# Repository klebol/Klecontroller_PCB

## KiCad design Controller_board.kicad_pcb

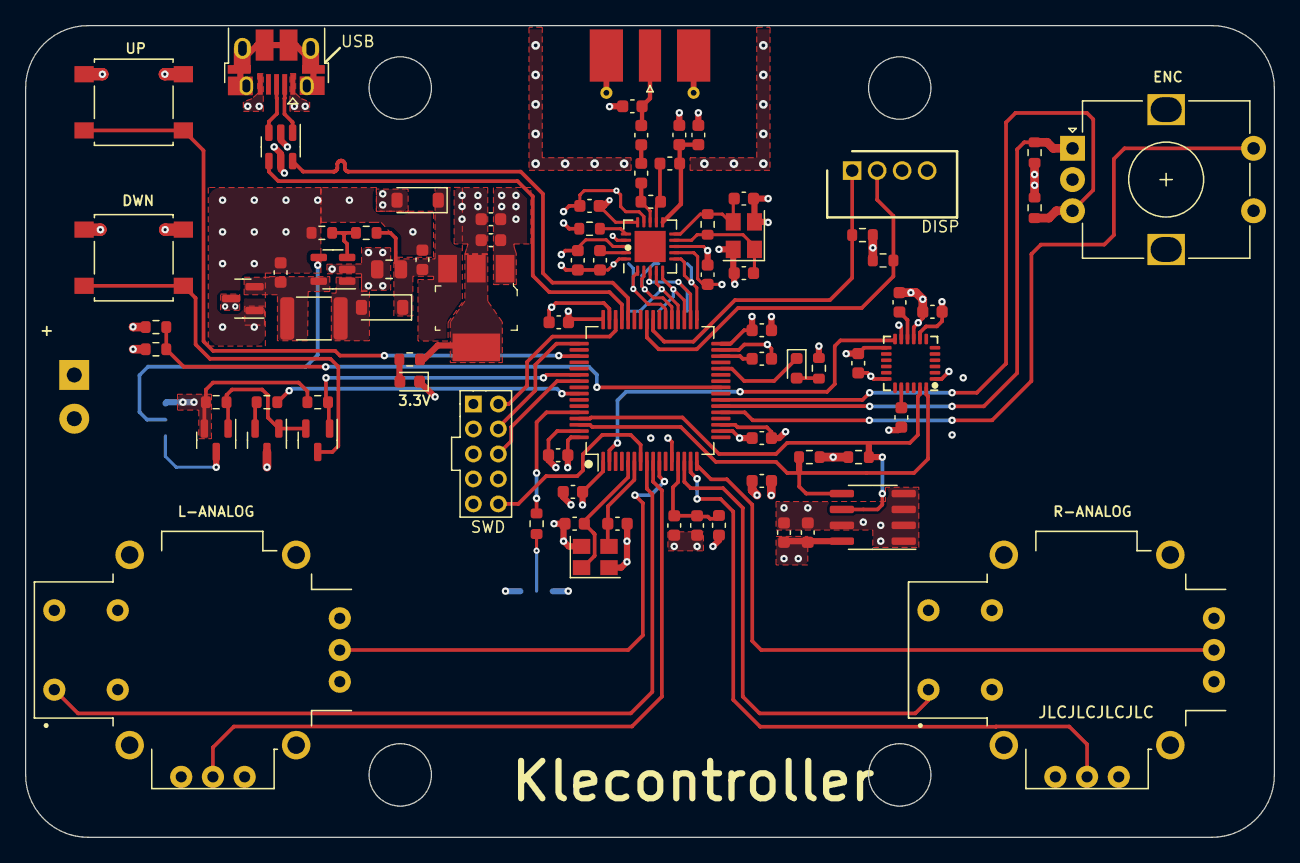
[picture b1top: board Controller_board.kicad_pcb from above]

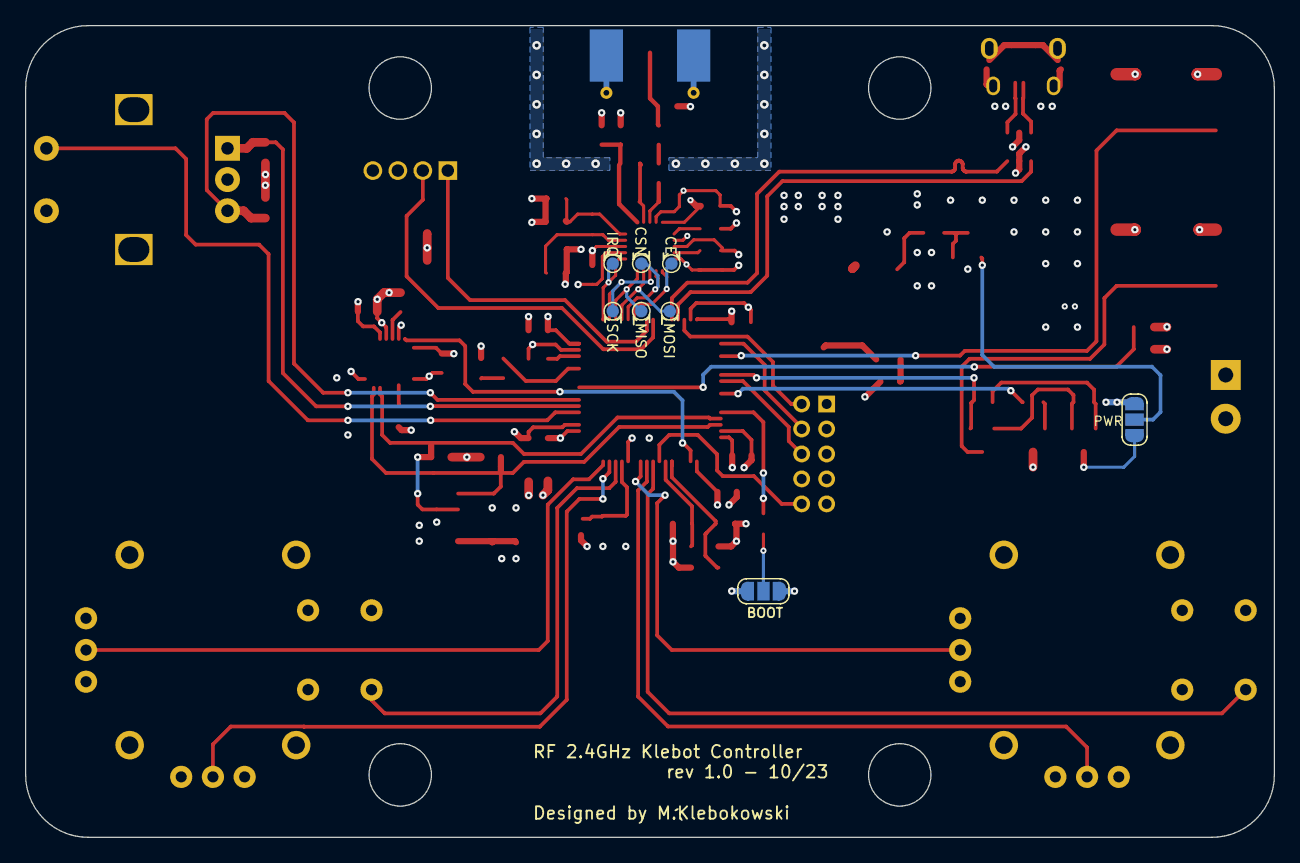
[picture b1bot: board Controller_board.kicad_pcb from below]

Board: 4 copper layers, 100.0 x 65.0 mm, 90 parts (8 on the bottom side), 65 nets.

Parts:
BT1: Battery; TerminalBlock_Phoenix_PT-1,5-2-3.5-H_1x02_P3.50mm_Horizontal
C1, C16: 4u7; C_0603_1608Metric
C2, C3, C4, C5, C6, C17, C18, C19, C21, C28, C31: 100n; C_0603_1608Metric
C7: 4u7 6.3V; C_0603_1608Metric
C8: 22uF 6.3V; C_0805_2012Metric
C9, C10: 100nF; C_0603_1608Metric
C11: 10uF; C_0603_1608Metric
C12: 1u; C_0603_1608Metric
C13, C20: 10n; C_0603_1608Metric
C14, C15, C24, C25: 10p; C_0603_1608Metric
C22: 1p5; C_0603_1608Metric
C23: 1p; C_0603_1608Metric
C26, C29: 2n2; C_0603_1608Metric
C27: 4p7; C_0603_1608Metric
C30: 33n; C_0603_1608Metric
C32: 2u2; C_0603_1608Metric
D1: BAT54C; SOT-23
D2, D5: 40V 1A; D_SOD-123
D3: LED RED; LED_0603_1608Metric
D4: LED BLUE; LED_0603_1608Metric
FB1: 120R; L_0603_1608Metric
J1: USB_B_Micro; USB_Micro-B_Amphenol_10103594-0001LF_Horizontal
J2: OLED_CONN; SHDR4W55P0X200_1X4_1000X500X530P
J3: SWD + UART; PinHeader_2x05_P2.00mm_Vertical
J4: SMA; SMA_Molex_73251-2120_EdgeMount_Horizontal
JP1: Powerup Mode; SolderJumper-3_P1.3mm_Open_RoundedPad1.0x1.5mm
L1: 4.7uH 650mA; L_1812_4532Metric
L3: 3n9; L_0603_1608Metric
L4: 8n2; L_0603_1608Metric
L5: 2n7; L_0603_1608Metric
Q1: BXT520P02M; SOT-23
Q2: DMP2045U; SOT-23
Q3: BC847-QR; SOT-23
R1: 5k62; R_0603_1608Metric
R2, R5, R16, R17, R18: 100k; R_0603_1608Metric
R3: 330R; R_0603_1608Metric
R4: 1k87; R_0603_1608Metric
R6: ?; R_0603_1608Metric
R7, R8, R9, R10: 2k2; R_0603_1608Metric
R11, R14, R15: 10k; R_0603_1608Metric
R12: 1M; R_0603_1608Metric
R13: 22k; R_0603_1608Metric
SW1: SW_SPDT; SolderJumper-3_P1.3mm_Open_RoundedPad1.0x1.5mm
SW2: Rotary Encoder; RotaryEncoder_Alps_EC12E-Switch_Vertical_H20mm
SW3, SW4: SW_Push; SW_SPST_B3S-1000
TP2: NRF_TestPoint_MOSI; TestPoint_Pad_D1.0mm
TP3: NRF_TestPoint_MISO; TestPoint_Pad_D1.0mm
TP4: NRF_TestPoint_SCK; TestPoint_Pad_D1.0mm
TP5: NRF_TestPoint_CSN; TestPoint_Pad_D1.0mm
TP6: NRF_TestPoint_CE; TestPoint_Pad_D1.0mm
TP7: NRF_TestPoint_IRQ; TestPoint_Pad_D1.0mm
U1: LD1117S33CTR; SOT-223
U2: MIC2288; TSOT-23-5
U3: USBLC6-2SC6; SOT-23-6
U4: STM32F401RBT6; LQFP-64_10x10mm_P0.5mm
U5: MPU-6050; InvenSense_QFN-24_4x4mm_P0.5mm
U6: nRF24L01P; QFN-20-1EP_4x4mm_P0.5mm_EP2.5x2.5mm
U7: M24C02-FMN; SOIC-8_3.9x4.9mm_P1.27mm
U8, U9: COM-09032; XDCR_COM-09032
Y1, Y2: 16 MHz; Crystal_SMD_3225-4Pin_3.2x2.5mm

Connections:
+3.3V: C1.1, C2.1, C3.1, C4.1, C5.1, C6.1, C10.1, C11.1, C17.1, C18.1, C19.1, C20.2, C21.2, C31.1, C32.1, FB1.1, J2.3, J3.1, R3.1, R6.2, R7.1, R8.1, R9.1, R10.1, R13.1, R14.1, R15.2, SW1.1 (A), U1.2 (VOUT), U1.4 (VOUT), U4.1 (VBAT), U4.19 (VDD), U4.32 (VDD), U4.48 (VDD), U4.64 (VDD), U5.8 (VLOGIC), U5.13 (VDD), U6.7 (VDD), U6.15 (VDD), U6.18 (VDD), U7.8 (VCC), U8.H1 (H+), U8.V1 (V+), U9.H1 (H+), U9.V1 (V+)
+5V: C8.1, C9.1, D2.1 (K), D5.1 (K), R1.1, U1.3 (VIN)
+BATT: BT1.1 (+), JP1.1 (A), Q1.3 (D), Q2.2 (S), R2.2, R16.1, R17.1
-BATT: BT1.2 (-), C1.2, C2.2, C3.2, C4.2, C5.2, C6.2, C7.2, C8.2, C9.2, C10.2, C11.2, C12.2, C13.2, C14.2, C15.2, C16.2, C17.2, C18.2, C19.2, C20.1, C21.1, C23.2, C24.2, C25.2, C26.1, C27.1, C28.1, C29.1, C30.2, C31.2, C32.2, D3.1 (K), J1.5 (GND), J2.4, J3.3, J3.5, J3.9, J4.2, Q1.1 (G), Q3.3 (E), R4.2, R5.1, SW1.3 (C), SW2.C, SW2.S2, SW3.1, SW4.1, U1.1 (GND), U2.2 (GND), U3.2 (GND), U4.12 (VSSA), U4.18 (VSS), U4.31 (VSS), U4.47 (VSS), U4.63 (VSS), U5.1 (CLKIN), U5.9 (AD0), U5.11 (FSYNC), U5.18 (GND), U6.8 (VSS), U6.14 (VSS), U6.17 (VSS), U6.20 (VSS), U7.1 (E0), U7.2 (E1), U7.3 (E2), U7.4 (VSS), U7.7 (~WC), U8.B2A (SEL-), U8.H3 (H-), U8.V3 (V-), U9.B2A (SEL-), U9.H3 (H-), U9.V3 (V-), Y1.2, Y1.4, Y2.2, Y2.4
BATTERY_ADC: R2.1, R5.2, U4.25 (PC5)
BOOT0: R11.1, U4.60 (BOOT0)
BUTTON_DOWN: D1.3, SW4.2
BUTTON_UP: SW3.2, U4.51 (PC10)
EN: JP1.2 (C), U2.4 (EN)
ENC_A: R14.2, SW2.A, U4.22 (PA6)
ENC_B: R15.1, SW2.B, U4.23 (PA7)
ENC_BUTTON: SW2.S1, U4.21 (PA5)
I2C_SCL: R9.2, U4.61 (PB8), U5.23 (SCL), U7.6 (SCL)
I2C_SDA: R10.2, U4.62 (PB9), U5.24 (SDA), U7.5 (SDA)
JOY1_ADC_X: U4.10 (PC2), U8.H2 (H)
JOY1_ADC_Y: U4.9 (PC1), U8.V2 (V)
JOY1_BUTTON: U4.8 (PC0), U8.B1A (SEL+)
JOY2_ADC_X: U4.16 (PA2), U9.H2 (H)
JOY2_ADC_Y: U4.15 (PA1), U9.V2 (V)
JOY2_BUTTON: U4.14 (PA0), U9.B1A (SEL+)
KEEP_ALIVE: R18.2, U4.57 (PB5)
LATCH_POWERUP: JP1.3 (B), Q2.3 (D)
MPU-6050_IRQ: U4.2 (PC13), U5.12 (INT)
NRF_ANT1: L4.2, L5.1, U6.12 (ANT1)
NRF_ANT2: L3.1, L4.1, U6.13 (ANT2)
NRF_CE: TP6.1, U4.38 (PC7), U6.1 (CE)
NRF_CSN: TP5.1, U4.37 (PC6), U6.2 (CSN)
NRF_IRQ: TP7.1, U4.33 (PB12), U6.6 (IRQ)
NRF_MISO: TP3.1, U4.35 (PB14), U6.5 (MISO)
NRF_MOSI: TP2.1, U4.36 (PB15), U6.4 (MOSI)
NRF_SCK: TP4.1, U4.34 (PB13), U6.3 (SCK)
NRF_VDD_PA: C26.2, C27.2, L5.2, U6.11 (VDD_PA)
NRF_XC1: C25.1, R12.2, U6.10 (XC1), Y2.3
NRF_XC2: C24.1, R12.1, U6.9 (XC2), Y2.1
NRST: J3.10, U4.7 (NRST)
unnamed: C22.1, L3.2
unnamed: C22.2, C23.1, J4.1
unnamed: D2.2 (A), L1.2, U2.1 (SW)
unnamed: D3.2 (A), R3.2
unnamed: D4.2 (A), R6.1
unnamed: D4.1 (K), U4.28 (PB2)
unnamed: C7.1, L1.1, Q1.2 (S), U2.5 (VIN)
unnamed: D1.2, Q2.1 (G), Q3.1 (C), R17.2
unnamed: Q3.2 (B), R18.1
unnamed: R11.2, SW1.2 (B)
unnamed: R1.2, R4.1, U2.3 (FB)
unnamed: C14.1, U4.5 (PH0), Y1.1
unnamed: C15.1, U4.6 (PH1), Y1.3
unnamed: C16.1, U4.30 (VCAP1)
unnamed: C12.1, C13.1, FB1.2, U4.13 (VREF+)
unnamed: C29.2, U5.20 (CPOUT)
unnamed: C28.2, U5.10 (REGOUT)
unnamed: C30.1, U6.19 (DVDD)
unnamed: R13.2, U6.16 (IREF)
OLED_SCL: J2.2, R7.2, U4.41 (PA8)
OLED_SDA: J2.1, R8.2, U4.40 (PC9)
Power_Btn: D1.1, R16.2, U4.54 (PD2)
SWCLK: J3.4, U4.49 (PA14)
SWDIO: J3.2, U4.46 (PA13)
SWO: J3.6, U4.55 (PB3)
USB_CONN_D+: J1.3 (D+), U3.3 (I/O2)
USB_CONN_D-: J1.2 (D-), U3.1 (I/O1)
USB_D+: U3.4 (I/O2), U4.45 (PA12)
USB_D-: U3.6 (I/O1), U4.44 (PA11)
V_USB: D5.2 (A), J1.1 (VBUS), U3.5 (VBUS)

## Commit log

2023-10-06 finalising layout
2023-11-11 Added Gerbers
